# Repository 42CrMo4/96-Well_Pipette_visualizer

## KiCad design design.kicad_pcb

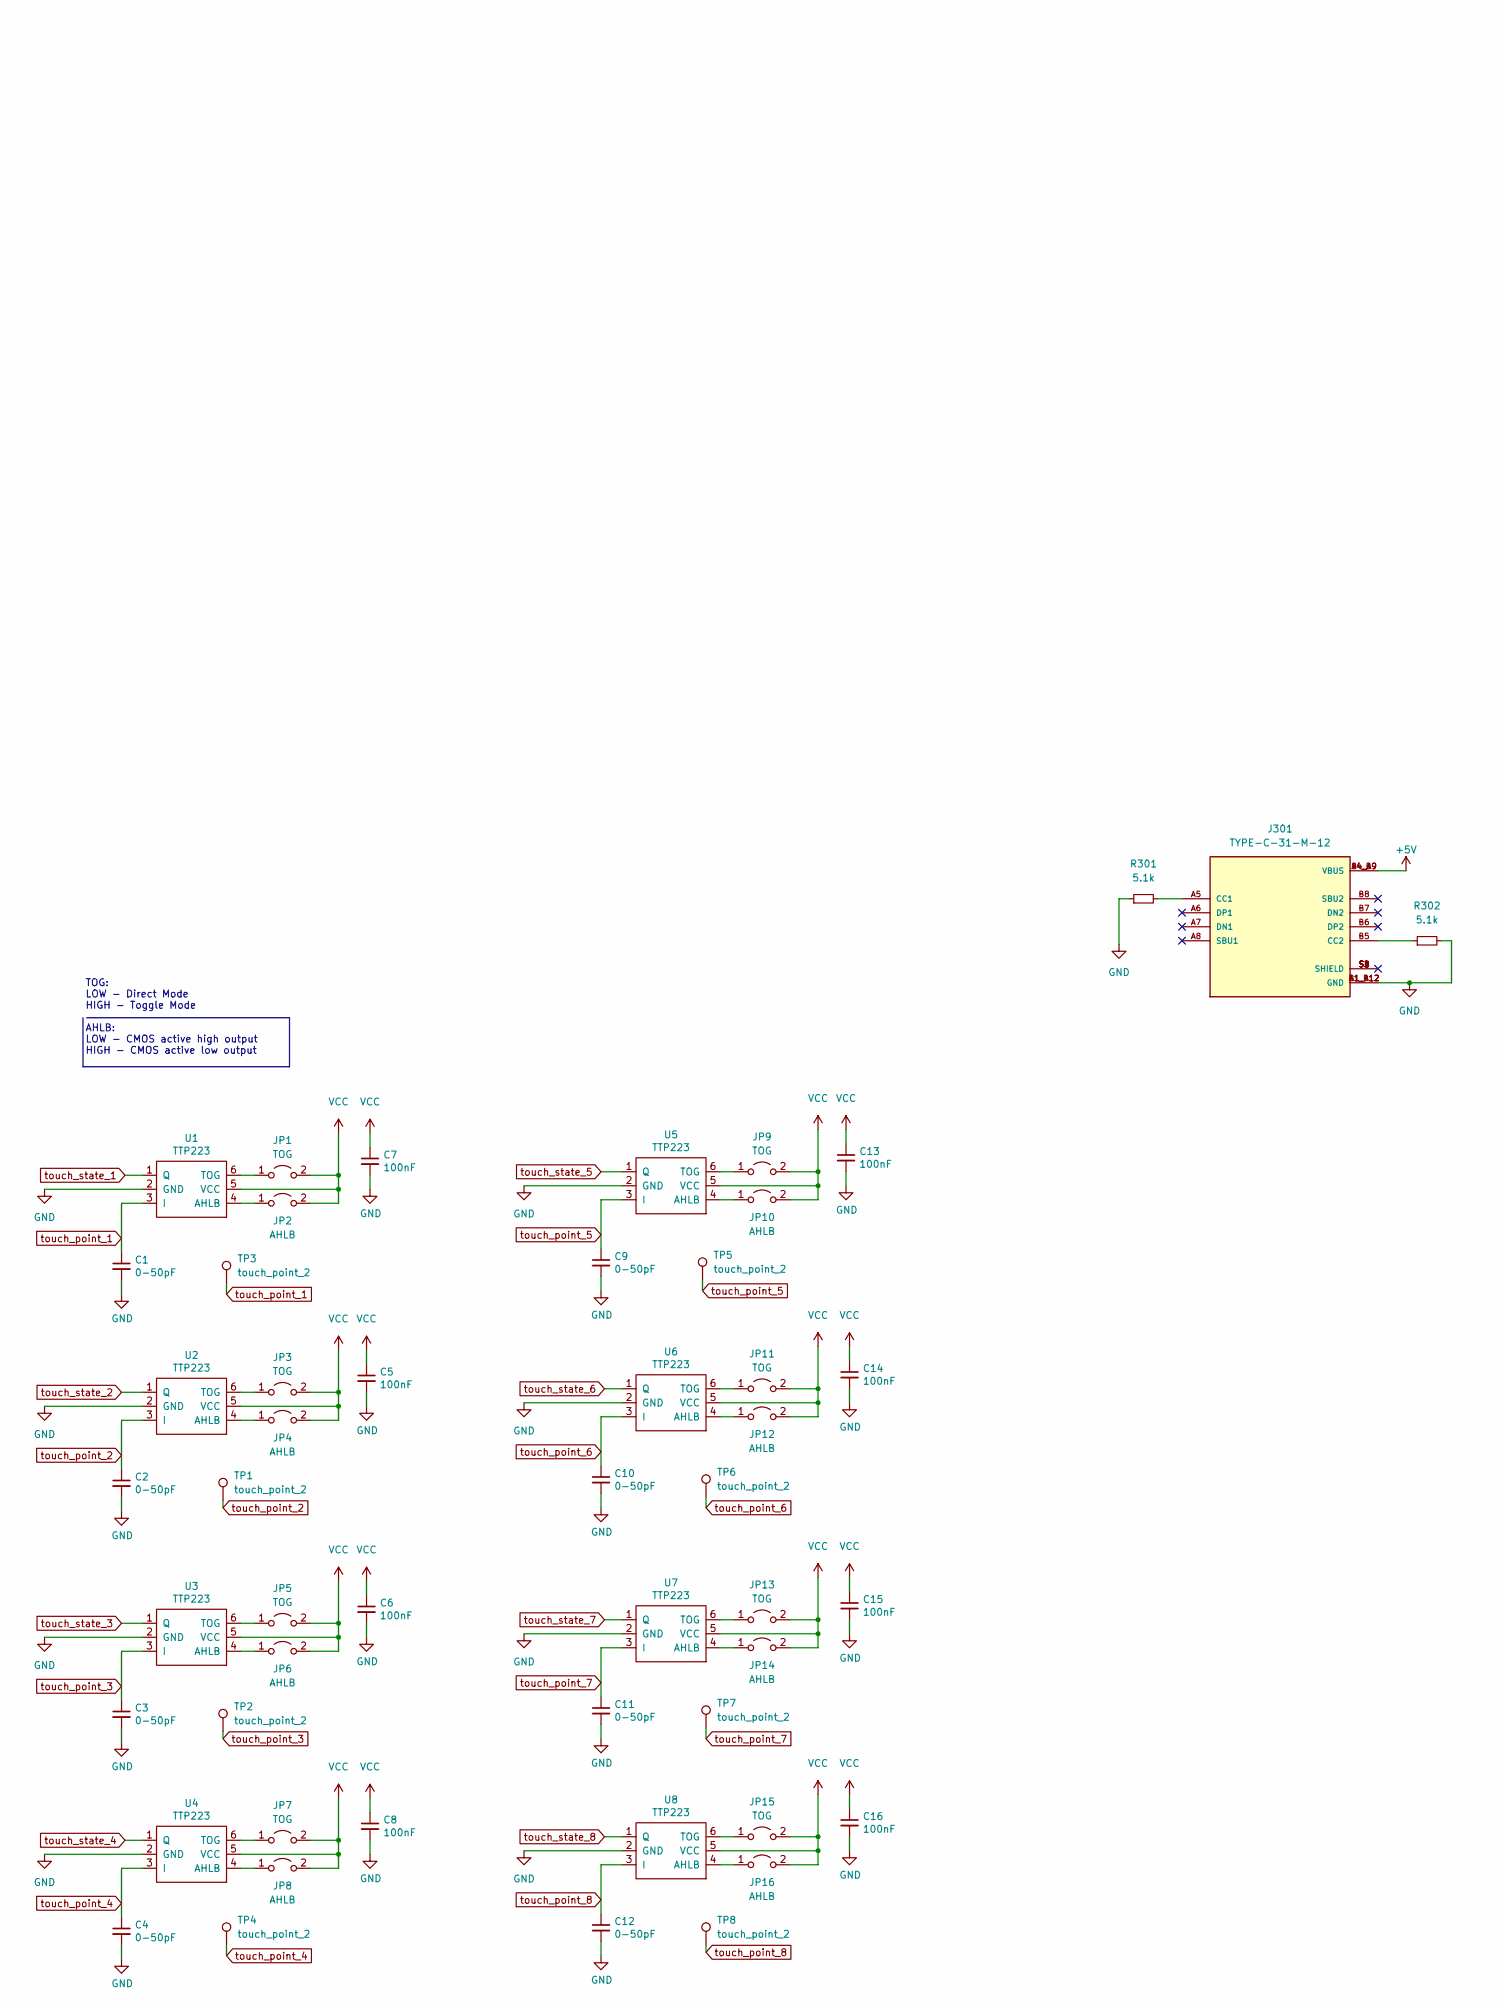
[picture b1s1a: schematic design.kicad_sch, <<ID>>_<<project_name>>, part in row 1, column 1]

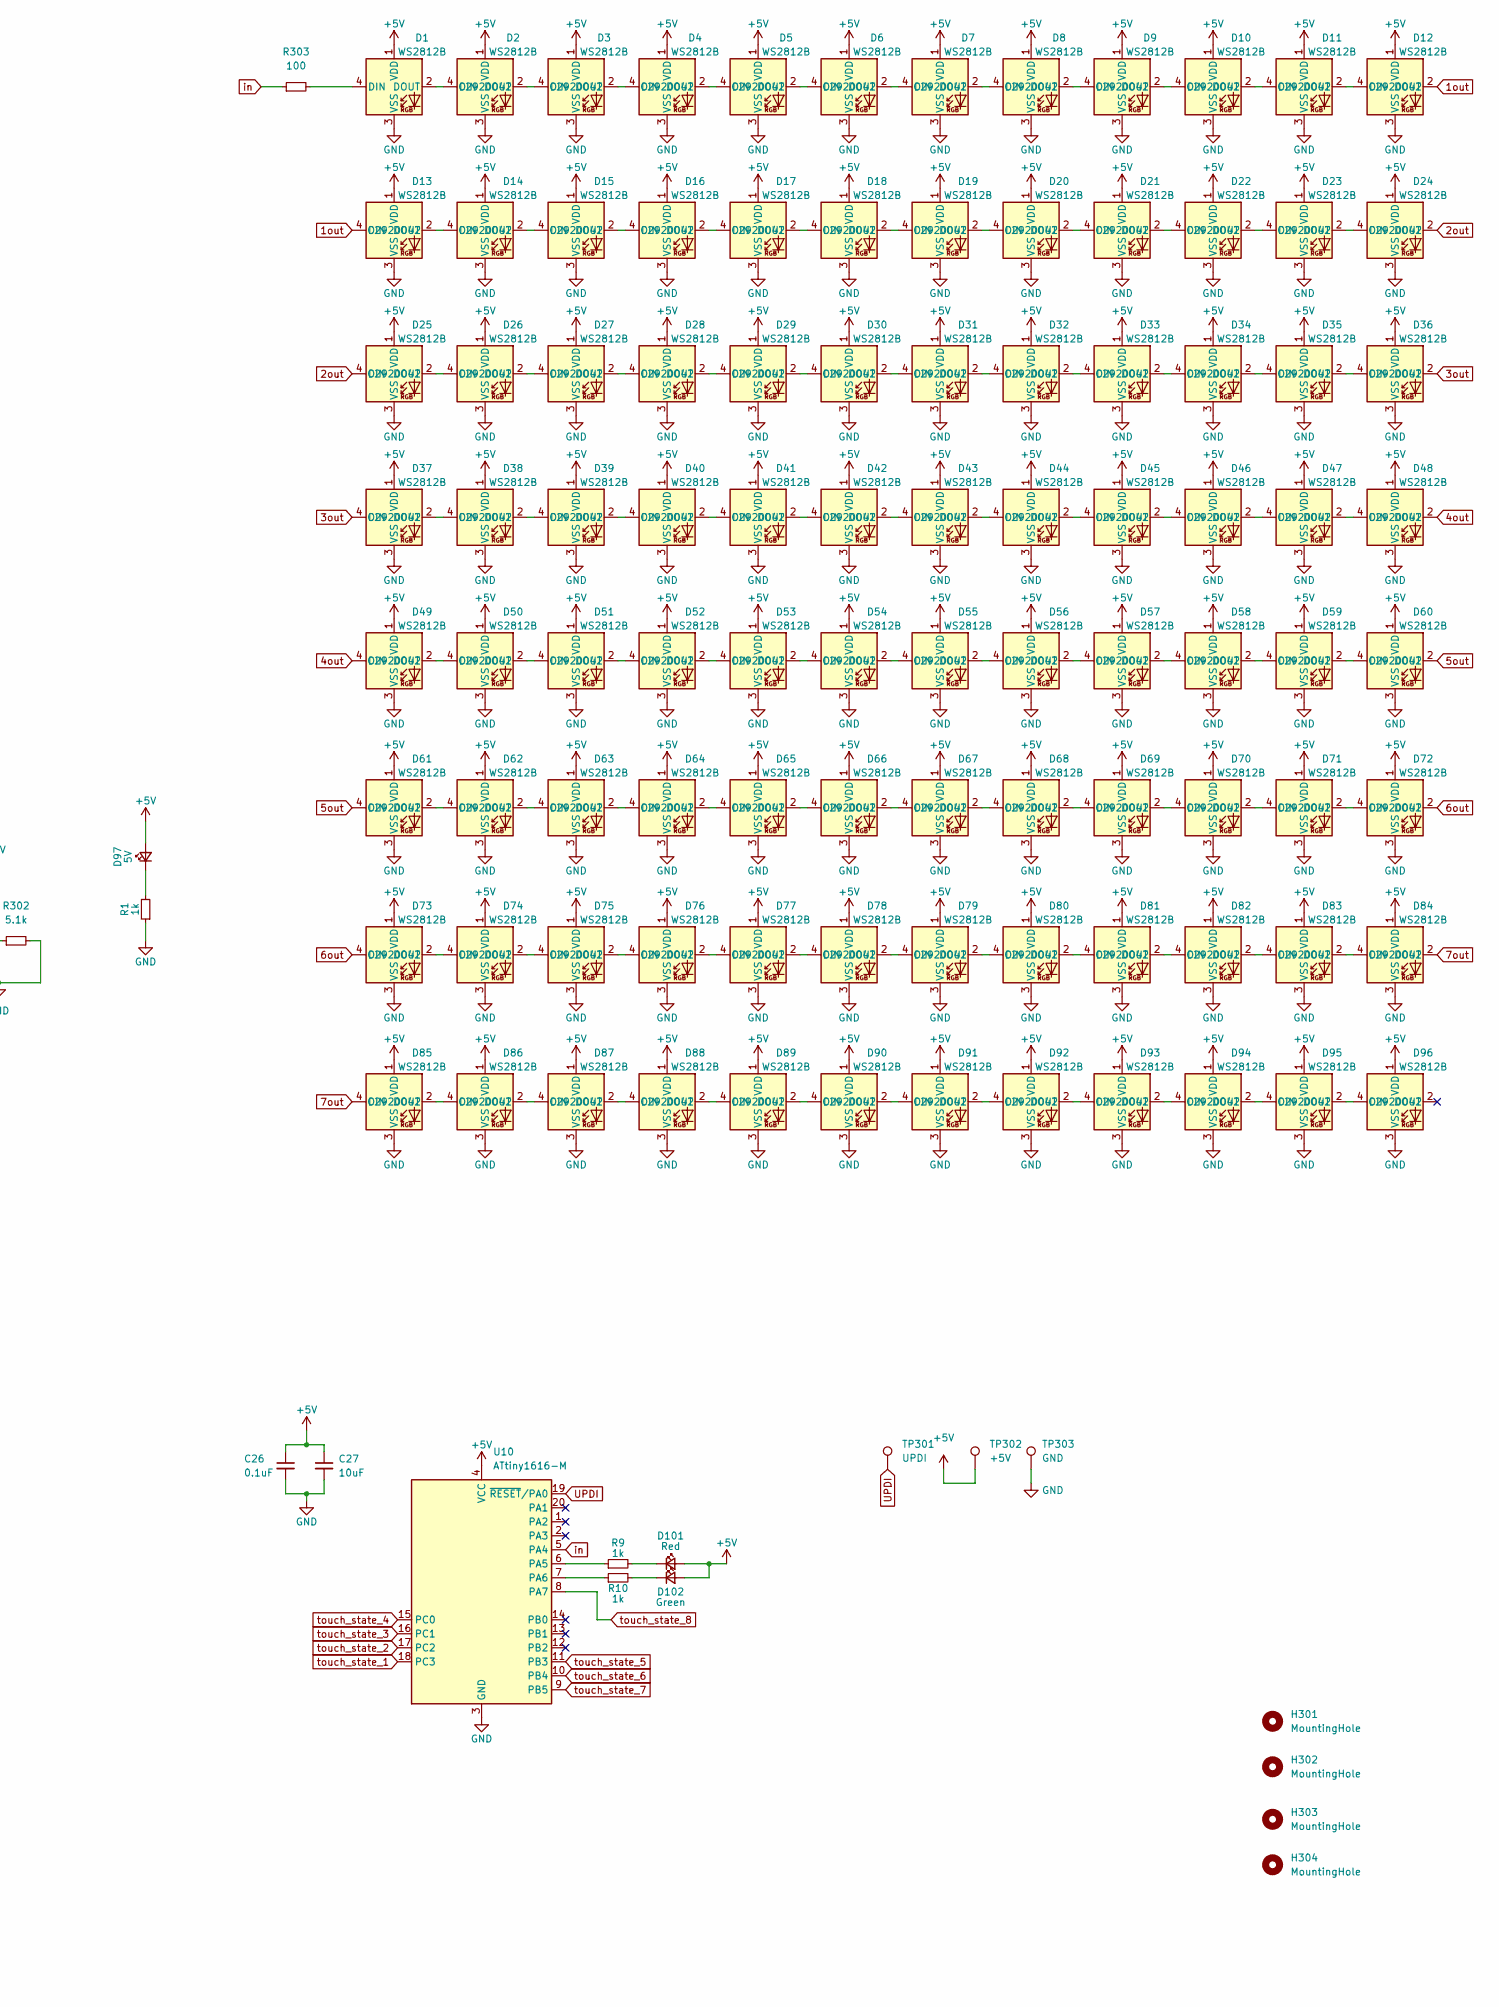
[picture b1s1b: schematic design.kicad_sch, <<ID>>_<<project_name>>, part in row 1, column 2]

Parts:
C1, C2, C3, C4, C9, C10, C11, C12: 0-50pF; C_0805_2012Metric
C5, C6, C7, C8, C13, C14, C15, C16: 100nF; C_0805_2012Metric
C26: 0.1uF; C_0805_2012Metric
C27: 10uF; C_0805_2012Metric
D1, D2, D3, D4, D5, D6, D7, D8, D9, D10, D11, D12, D13, D14, D15, D16, D17, D18, D19, D20, D21, D22, D23, D24, D25, D26, D27, D28, D29, D30, D31, D32, D33, D34, D35, D36, D37, D38, D39, D40, D41, D42, D43, D44, D45, D46, D47, D48, D49, D50, D51, D52, D53, D54, D55, D56, D57, D58, D59, D60, D61, D62, D63, D64, D65, D66, D67, D68, D69, D70, D71, D72, D73, D74, D75, D76, D77, D78, D79, D80, D81, D82, D83, D84, D85, D86, D87, D88, D89, D90, D91, D92, D93, D94, D95, D96: WS2812B; LED_WS2812B_PLCC4_5.0x5.0mm_P3.2mm; LCSC C2920042
D97: 5V; LED_0603_1608Metric
D101: Red; LED_0603_1608Metric
D102: Green; LED_0603_1608Metric
H301, H302, H303, H304: MountingHole; MountingHole_2.7mm_M2.5
J301: TYPE-C-31-M-12; TYPE-C-31-M-12_HRO_TYPE-C-31-M-12; PARTREV 2020.12.08
JP1, JP3, JP5, JP7, JP9, JP11, JP13, JP15: TOG; SolderJumper-2_P1.3mm_Open_RoundedPad1.0x1.5mm
JP2, JP4, JP6, JP8, JP10, JP12, JP14, JP16: AHLB; SolderJumper-2_P1.3mm_Open_RoundedPad1.0x1.5mm
R1, R9, R10: 1k; R_0805_2012Metric
R301, R302: 5.1k; R_0805_2012Metric
R303: 100; R_0805_2012Metric
TP1, TP2, TP3, TP4, TP5, TP6, TP7, TP8: touch_point_2
TP301: UPDI; TestPoint_Pad_3.0x3.0mm
TP302: +5V; TestPoint_Pad_3.0x3.0mm
TP303: GND; TestPoint_Pad_3.0x3.0mm
U1, U2, U3, U4, U5, U6, U7, U8: TTP223; SOT-23-6
U10: ATtiny1616-M; VQFN-20-1EP_3x3mm_P0.4mm_EP1.7x1.7mm

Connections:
1out: D12.2 (DOUT), D13.4 (DIN)
2out: D24.2 (DOUT), D25.4 (DIN)
3out: D36.2 (DOUT), D37.4 (DIN)
4out: D48.2 (DOUT), D49.4 (DIN)
5out: D60.2 (DOUT), D61.4 (DIN)
6out: D72.2 (DOUT), D73.4 (DIN)
7out: D84.2 (DOUT), D85.4 (DIN)
GND: C1.2, C2.2, C3.2, C4.2, C5.2, C6.2, C7.2, C8.2, C9.2, C10.2, C11.2, C12.2, C13.2, C14.2, C15.2, C16.2, C26.2, C27.2, D1.3 (VSS), D2.3 (VSS), D3.3 (VSS), D4.3 (VSS), D5.3 (VSS), D6.3 (VSS), D7.3 (VSS), D8.3 (VSS), D9.3 (VSS), D10.3 (VSS), D11.3 (VSS), D12.3 (VSS), D13.3 (VSS), D14.3 (VSS), D15.3 (VSS), D16.3 (VSS), D17.3 (VSS), D18.3 (VSS), D19.3 (VSS), D20.3 (VSS), D21.3 (VSS), D22.3 (VSS), D23.3 (VSS), D24.3 (VSS), D25.3 (VSS), D26.3 (VSS), D27.3 (VSS), D28.3 (VSS), D29.3 (VSS), D30.3 (VSS), D31.3 (VSS), D32.3 (VSS), D33.3 (VSS), D34.3 (VSS), D35.3 (VSS), D36.3 (VSS), D37.3 (VSS), D38.3 (VSS), D39.3 (VSS), D40.3 (VSS), D41.3 (VSS), D42.3 (VSS), D43.3 (VSS), D44.3 (VSS), D45.3 (VSS), D46.3 (VSS), D47.3 (VSS), D48.3 (VSS), D49.3 (VSS), D50.3 (VSS), D51.3 (VSS), D52.3 (VSS), D53.3 (VSS), D54.3 (VSS), D55.3 (VSS), D56.3 (VSS), D57.3 (VSS), D58.3 (VSS), D59.3 (VSS), D60.3 (VSS), D61.3 (VSS), D62.3 (VSS), D63.3 (VSS), D64.3 (VSS), D65.3 (VSS), D66.3 (VSS), D67.3 (VSS), D68.3 (VSS), D69.3 (VSS), D70.3 (VSS), D71.3 (VSS), D72.3 (VSS), D73.3 (VSS), D74.3 (VSS), D75.3 (VSS), D76.3 (VSS), D77.3 (VSS), D78.3 (VSS), D79.3 (VSS), D80.3 (VSS), D81.3 (VSS), D82.3 (VSS), D83.3 (VSS), D84.3 (VSS), D85.3 (VSS), D86.3 (VSS), D87.3 (VSS), D88.3 (VSS), D89.3 (VSS), D90.3 (VSS), D91.3 (VSS), D92.3 (VSS), D93.3 (VSS), D94.3 (VSS), D95.3 (VSS), D96.3 (VSS), J301.A1_B12 (GND), J301.B1_A12 (GND), R1.1, R301.1, R302.2, TP303.1, U1.2 (GND), U2.2 (GND), U3.2 (GND), U4.2 (GND), U5.2 (GND), U6.2 (GND), U7.2 (GND), U8.2 (GND), U10.3 (GND), U10.21 (GND)
unnamed: D1.2 (DOUT), D2.4 (DIN)
unnamed: D1.4 (DIN), R303.2
unnamed: D2.2 (DOUT), D3.4 (DIN)
unnamed: D3.2 (DOUT), D4.4 (DIN)
unnamed: D4.2 (DOUT), D5.4 (DIN)
unnamed: D5.2 (DOUT), D6.4 (DIN)
unnamed: D6.2 (DOUT), D7.4 (DIN)
unnamed: D7.2 (DOUT), D8.4 (DIN)
unnamed: D8.2 (DOUT), D9.4 (DIN)
unnamed: D10.2 (DOUT), D11.4 (DIN)
unnamed: D9.2 (DOUT), D10.4 (DIN)
unnamed: D11.2 (DOUT), D12.4 (DIN)
unnamed: D13.2 (DOUT), D14.4 (DIN)
unnamed: D14.2 (DOUT), D15.4 (DIN)
unnamed: D15.2 (DOUT), D16.4 (DIN)
unnamed: D16.2 (DOUT), D17.4 (DIN)
unnamed: D17.2 (DOUT), D18.4 (DIN)
unnamed: D18.2 (DOUT), D19.4 (DIN)
unnamed: D19.2 (DOUT), D20.4 (DIN)
unnamed: D20.2 (DOUT), D21.4 (DIN)
unnamed: D21.2 (DOUT), D22.4 (DIN)
unnamed: D22.2 (DOUT), D23.4 (DIN)
unnamed: D23.2 (DOUT), D24.4 (DIN)
unnamed: D25.2 (DOUT), D26.4 (DIN)
unnamed: D26.2 (DOUT), D27.4 (DIN)
unnamed: D27.2 (DOUT), D28.4 (DIN)
unnamed: D28.2 (DOUT), D29.4 (DIN)
unnamed: D29.2 (DOUT), D30.4 (DIN)
unnamed: D30.2 (DOUT), D31.4 (DIN)
unnamed: D31.2 (DOUT), D32.4 (DIN)
unnamed: D32.2 (DOUT), D33.4 (DIN)
unnamed: D33.2 (DOUT), D34.4 (DIN)
unnamed: D34.2 (DOUT), D35.4 (DIN)
unnamed: D35.2 (DOUT), D36.4 (DIN)
unnamed: D37.2 (DOUT), D38.4 (DIN)
unnamed: D38.2 (DOUT), D39.4 (DIN)
unnamed: D39.2 (DOUT), D40.4 (DIN)
unnamed: D40.2 (DOUT), D41.4 (DIN)
unnamed: D41.2 (DOUT), D42.4 (DIN)
unnamed: D42.2 (DOUT), D43.4 (DIN)
unnamed: D43.2 (DOUT), D44.4 (DIN)
unnamed: D44.2 (DOUT), D45.4 (DIN)
unnamed: D45.2 (DOUT), D46.4 (DIN)
unnamed: D46.2 (DOUT), D47.4 (DIN)
unnamed: D47.2 (DOUT), D48.4 (DIN)
unnamed: D49.2 (DOUT), D50.4 (DIN)
unnamed: D50.2 (DOUT), D51.4 (DIN)
unnamed: D51.2 (DOUT), D52.4 (DIN)
unnamed: D52.2 (DOUT), D53.4 (DIN)
unnamed: D53.2 (DOUT), D54.4 (DIN)
unnamed: D54.2 (DOUT), D55.4 (DIN)
unnamed: D55.2 (DOUT), D56.4 (DIN)
unnamed: D56.2 (DOUT), D57.4 (DIN)
unnamed: D57.2 (DOUT), D58.4 (DIN)
unnamed: D58.2 (DOUT), D59.4 (DIN)
unnamed: D59.2 (DOUT), D60.4 (DIN)
unnamed: D61.2 (DOUT), D62.4 (DIN)
unnamed: D62.2 (DOUT), D63.4 (DIN)
unnamed: D63.2 (DOUT), D64.4 (DIN)
unnamed: D64.2 (DOUT), D65.4 (DIN)
unnamed: D65.2 (DOUT), D66.4 (DIN)
unnamed: D66.2 (DOUT), D67.4 (DIN)
unnamed: D67.2 (DOUT), D68.4 (DIN)
unnamed: D68.2 (DOUT), D69.4 (DIN)
unnamed: D69.2 (DOUT), D70.4 (DIN)
unnamed: D70.2 (DOUT), D71.4 (DIN)
unnamed: D71.2 (DOUT), D72.4 (DIN)
unnamed: D73.2 (DOUT), D74.4 (DIN)
unnamed: D74.2 (DOUT), D75.4 (DIN)
unnamed: D75.2 (DOUT), D76.4 (DIN)
unnamed: D76.2 (DOUT), D77.4 (DIN)
unnamed: D77.2 (DOUT), D78.4 (DIN)
unnamed: D78.2 (DOUT), D79.4 (DIN)
unnamed: D79.2 (DOUT), D80.4 (DIN)
unnamed: D80.2 (DOUT), D81.4 (DIN)
unnamed: D81.2 (DOUT), D82.4 (DIN)
unnamed: D82.2 (DOUT), D83.4 (DIN)
unnamed: D83.2 (DOUT), D84.4 (DIN)
unnamed: D85.2 (DOUT), D86.4 (DIN)
unnamed: D86.2 (DOUT), D87.4 (DIN)
unnamed: D87.2 (DOUT), D88.4 (DIN)
unnamed: D88.2 (DOUT), D89.4 (DIN)
unnamed: D89.2 (DOUT), D90.4 (DIN)
unnamed: D90.2 (DOUT), D91.4 (DIN)
unnamed: D91.2 (DOUT), D92.4 (DIN)
unnamed: D92.2 (DOUT), D93.4 (DIN)
unnamed: D93.2 (DOUT), D94.4 (DIN)
unnamed: D94.2 (DOUT), D95.4 (DIN)
unnamed: D95.2 (DOUT), D96.4 (DIN)
unnamed: D97.1 (K), R1.2
unnamed: D101.1 (K), R9.2
unnamed: D102.1 (K), R10.2
unnamed: J301.A5 (CC1), R301.2
unnamed: J301.B5 (CC2), R302.1
unnamed: JP1.1 (A), U1.6 (TOG)
unnamed: JP2.1 (A), U1.4 (AHLB)
unnamed: JP3.1 (A), U2.6 (TOG)
unnamed: JP4.1 (A), U2.4 (AHLB)
unnamed: JP5.1 (A), U3.6 (TOG)
unnamed: JP6.1 (A), U3.4 (AHLB)
unnamed: JP7.1 (A), U4.6 (TOG)
unnamed: JP8.1 (A), U4.4 (AHLB)
unnamed: JP9.1 (A), U5.6 (TOG)
unnamed: JP10.1 (A), U5.4 (AHLB)
unnamed: JP11.1 (A), U6.6 (TOG)
unnamed: JP12.1 (A), U6.4 (AHLB)
unnamed: JP13.1 (A), U7.6 (TOG)
unnamed: JP14.1 (A), U7.4 (AHLB)
unnamed: JP15.1 (A), U8.6 (TOG)
unnamed: JP16.1 (A), U8.4 (AHLB)
unnamed: R9.1, U10.6 (PA5)
unnamed: R10.1, U10.7 (PA6)
UPDI: TP301.1, U10.19 (~RESET/PA0)
in: R303.1, U10.5 (PA4)
touch_point_1: C1.1, TP3.1, U1.3 (I)
touch_point_2: C2.1, TP1.1, U2.3 (I)
touch_point_3: C3.1, TP2.1, U3.3 (I)
touch_point_4: C4.1, TP4.1, U4.3 (I)
touch_point_5: C9.1, TP5.1, U5.3 (I)
touch_point_6: C10.1, TP6.1, U6.3 (I)
touch_point_7: C11.1, TP7.1, U7.3 (I)
touch_point_8: C12.1, TP8.1, U8.3 (I)
touch_state_1: U1.1 (Q), U10.18 (PC3)
touch_state_2: U2.1 (Q), U10.17 (PC2)
touch_state_3: U3.1 (Q), U10.16 (PC1)
touch_state_4: U4.1 (Q), U10.15 (PC0)
touch_state_5: U5.1 (Q), U10.11 (PB3)
touch_state_6: U6.1 (Q), U10.10 (PB4)
touch_state_7: U7.1 (Q), U10.9 (PB5)
touch_state_8: U8.1 (Q), U10.8 (PA7)

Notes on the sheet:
TOG: LOW - Direct Mode HIGH - Toggle Mode AHLB: LOW - CMOS active high output HIGH - CMOS active low output

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
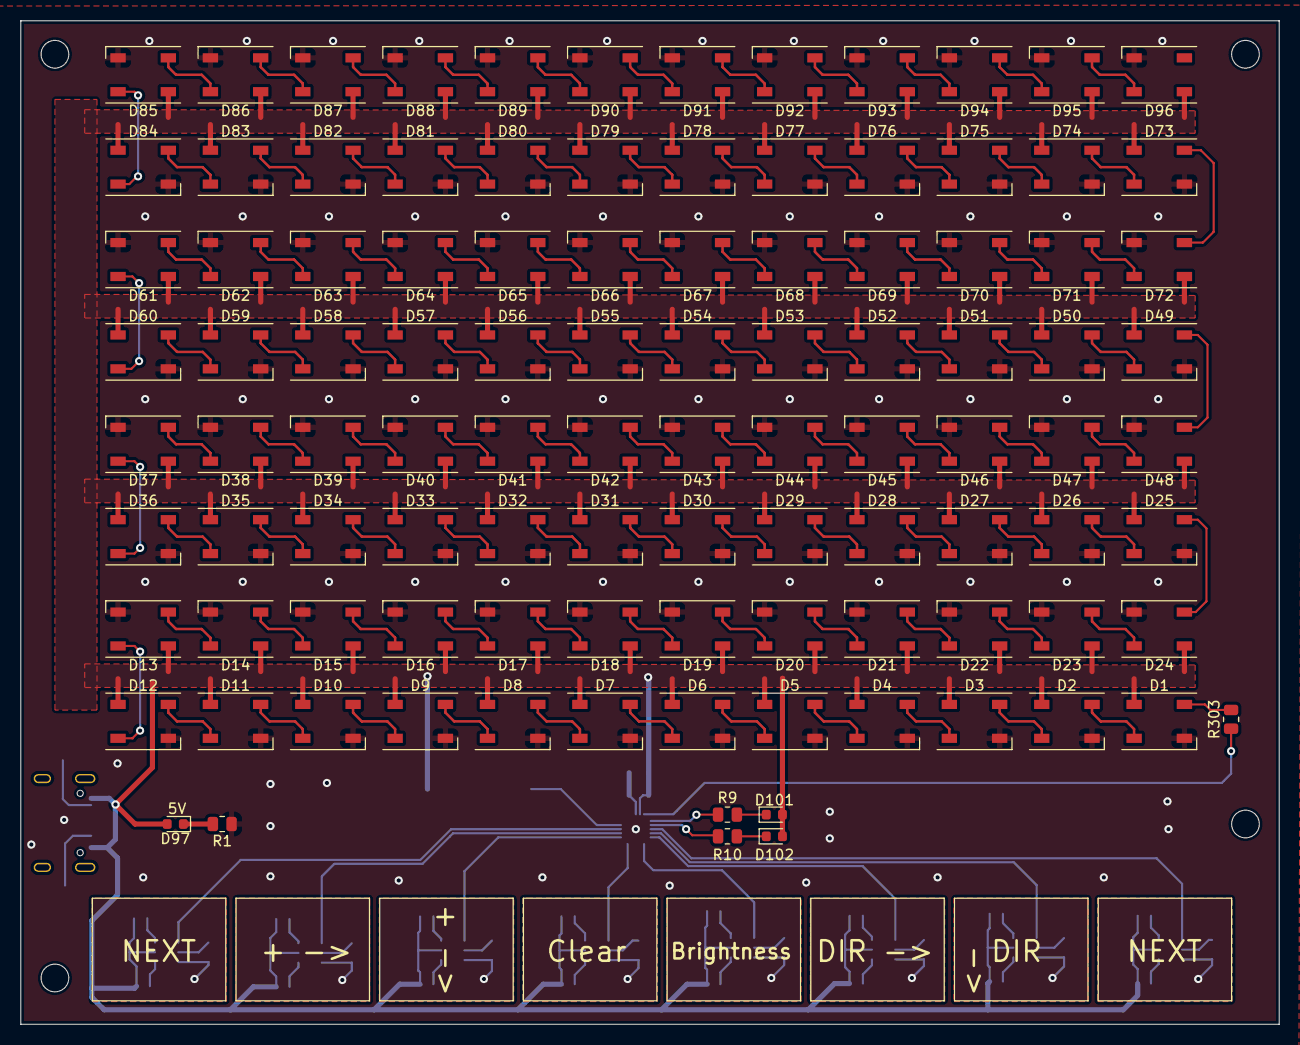
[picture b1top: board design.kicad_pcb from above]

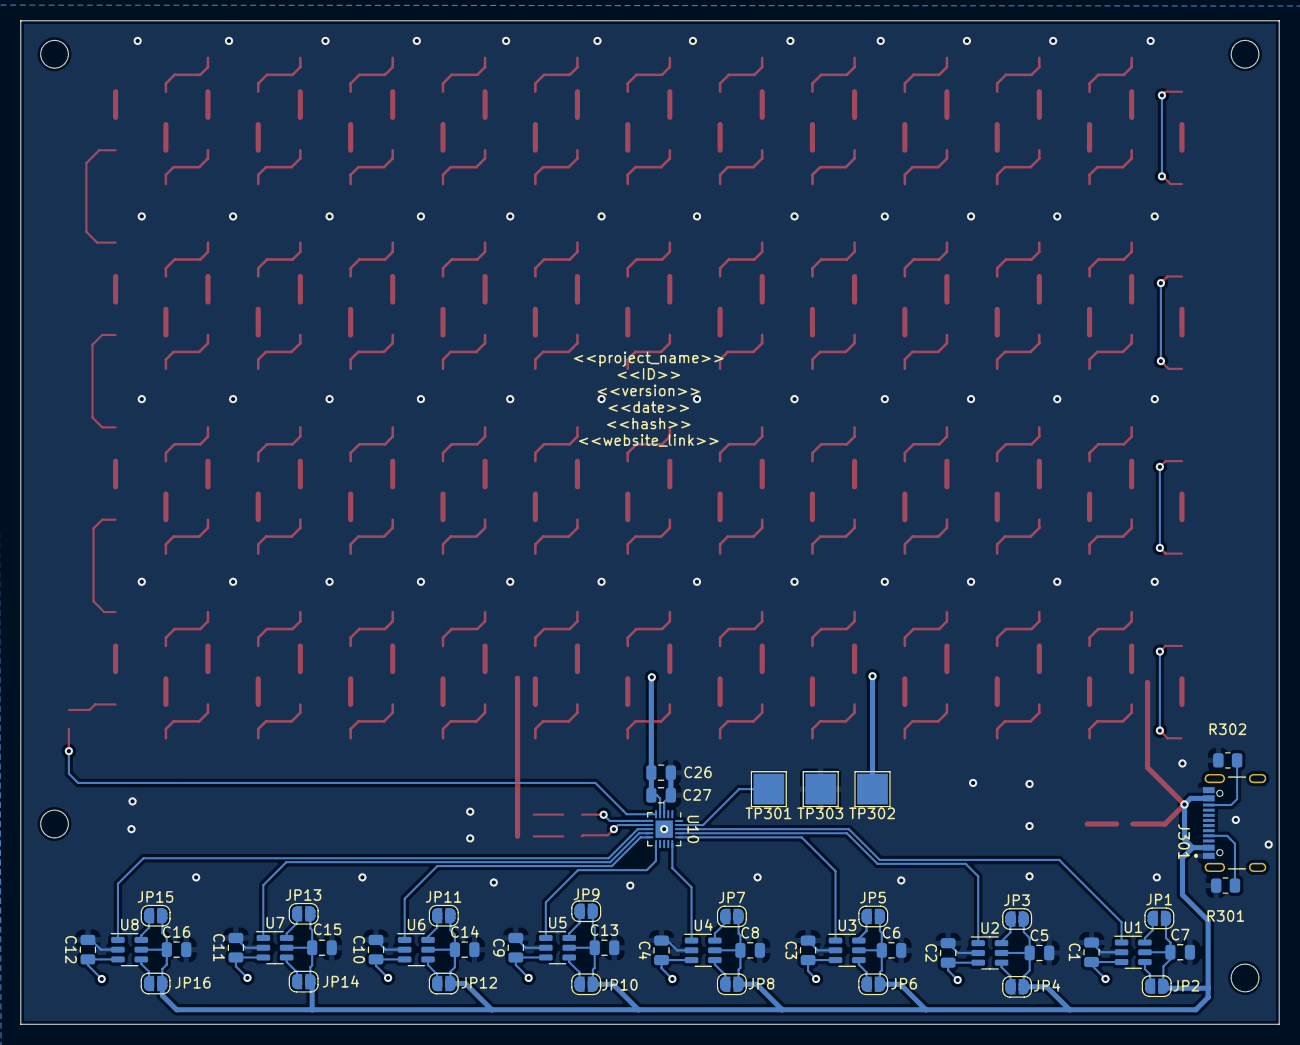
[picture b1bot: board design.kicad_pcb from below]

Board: 2 copper layers, 122.6 x 97.8 mm, 156 parts (49 on the bottom side), 139 nets.

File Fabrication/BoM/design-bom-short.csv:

Row,Description,Part,References,Value,Footprint,Quantity Per PCB,Status,Datasheet,LCSC,MF,MAXIMUM_PACKAGE_HEIGHT,Package,Price,Check_prices,STANDARD,PARTREV,SnapEDA_Link,MP,SNAPEDA_PN,Availability,MANUFACTURER
1,"Unpolarized capacitor, small symbol",C_Small,C5 C6 C7 C8 C13 C14 C15 C16 C26,100nF,C_0805_2012Metric,9, ,~,,,,,,,,,,,,,
2,"Unpolarized capacitor, small symbol",C_Small,C27,10uF,C_0805_2012Metric,1, ,~,,,,,,,,,,,,,
3,"Unpolarized capacitor, small symbol",C_Small,C1 C2 C3 C4 C9 C10 C11 C12,0-50pF,C_0805_2012Metric,8, ,~,,,,,,,,,,,,,
4,"Light emitting diode, small symbol",LED_Small,D97,5V,LED_0603_1608Metric,1, ,~,,,,,,,,,,,,,
5,"Light emitting diode, small symbol",LED_Small,D102,Green,LED_0603_1608Metric,1, ,~,,,,,,,,,,,,,
6,"Light emitting diode, small symbol",LED_Small,D101,Red,LED_0603_1608Metric,1, ,~,,,,,,,,,,,,,
7,RGB LED with integrated controller,WS2812B,D1 D2 D3 D4 D5 D6 D7 D8 D9 D10 D11 D12 D13 D14 D15 D16 D17 D18 D19 D20 D21 D22 D23 D24 D25 D26 D27 D28 D29 D30 D31 D32 D33 D34 D35 D36 D37 D38 D39 D40 D41 D42 D43 D44 D45 D46 D47 D48 D49 D50 D51 D52 D53 D54 D55 D56 D57 D58 D59 D60 D61 D62 D63 D64 D65 D66 D67 D68 D69 D70 D71 D72 D73 D74 D75 D76 D77 D78 D79 D80 D81 D82 D83 D84 D85 D86 D87 D88 D89 D90 D91 D92 D93 D94 D95 D96,WS2812B,LED_WS2812B_PLCC4_5.0x5.0mm_P3.2mm,96, ,https://cdn-shop.adafruit.com/datasheets/WS2812B.pdf,C2920042,,,,,,,,,,,,
8,USB Connectors 24 Receptacle 1 8.94*7.3mm RoHS,TYPE-C-31-M-12,J301,TYPE-C-31-M-12,TYPE-C-31-M-12_HRO_TYPE-C-31-M-12,1, ,,,"HRO Electronics Co., Ltd.",3.26 mm,Package,None,https://www.snapeda.com/parts/TYPE-C-31-M-12/HRO+Electronics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,Manufacturer Recommendations,2020.12.08,https://www.snapeda.com/parts/TYPE-C-31-M-12/HRO+Electronics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,TYPE-C-31-M-12,TYPE-C-31-M-12,Not in stock,"HRO Electronics Co., Ltd."
9,"Jumper, 2-pole, open",Jumper_2_Open,JP2 JP4 JP6 JP8 JP10 JP12 JP14 JP16,AHLB,SolderJumper-2_P1.3mm_Open_RoundedPad1.0x1.5mm,8, ,~,,,,,,,,,,,,,
10,"Jumper, 2-pole, open",Jumper_2_Open,JP1 JP3 JP5 JP7 JP9 JP11 JP13 JP15,TOG,SolderJumper-2_P1.3mm_Open_RoundedPad1.0x1.5mm,8, ,~,,,,,,,,,,,,,
11,"Resistor, small symbol",R_Small,R303,100,R_0805_2012Metric,1, ,~,,,,,,,,,,,,,
12,"Resistor, small symbol",R_Small,R1 R9 R10,1k,R_0805_2012Metric,3, ,~,,,,,,,,,,,,,
13,"Resistor, small symbol",R_Small,R301 R302,5.1k,R_0805_2012Metric,2, ,~,,,,,,,,,,,,,
14,"20MHz, 16kB Flash, 2kB SRAM, 256B EEPROM, VQFN-20",ATtiny1616-M,U10,ATtiny1616-M,VQFN-20-1EP_3x3mm_P0.4mm_EP1.7x1.7mm,1, ,http://ww1.microchip.com/downloads/en/DeviceDoc/ATtiny3216_A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,,,,,,,,,,,,,
15,,TTP223,U1 U2 U3 U4 U5 U6 U7 U8,TTP223,SOT-23-6,8, ,,,,,,,,,,,,,,

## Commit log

2024-04-14 remove diff
2024-04-14 use 8de6343 as workflow commit
2024-04-14 use tag v6.0 instead of commit
2024-05-04 lower clearance
2024-05-06 change to QFN 1616
2024-05-18 some confusing LED double footprints
2024-05-18 new layout
2024-05-18 add JLC output
2024-05-18 use v8 workflow?
2024-05-18 use kicad 8 branch of workflow
2024-05-18 upadte
2024-05-18 added lcsc number test
2024-05-18 update all LEDs with LCSC #
2024-05-19 mounting holes
2024-05-19 Test Ausrichtung
2024-05-19 mounting hole
2024-05-19 silkscreen correction
2024-05-19 Archive & Renew release docs
2024-06-06 added HW version Info
2024-06-06 Add Summary of code
2024-06-06 start to implement the button press feature
2024-06-06 Add simulated button press over UART
    Updated the code to include functionality for simulating a button press via UART. Now, besides physical button presses on pin 4, the program also responds to the character 'p' received over serial co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
2024-06-06 Factor out LED matrix definition to a separate file
    Created matrix.h to define the LED matrix separately from the main code. Updated the main code to reference the matrix from matrix.h, improving modularity and readability.
2024-06-06 Add brightness control via button and serial input
    Updated the code to include functionality for toggling between different brightness levels (10, 30, 50, 80, 100) using a second button and serial input. Added definitions for the brightness button an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
2024-06-06 Fix brightness control in lightUpMatrix function
    Updated the lightUpMatrix function to properly set brightness based on the currentBrightnessIndex. The brightness value is now correctly mapped and passed to the strip.setBrightness() call, ensuring 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
2024-06-06 Fix brightness setting and update immediately
    Modified the lightUpMatrix function to set the brightness after setting LED colors. Added a setBrightness function to update the brightness immediately when the brightness button is pressed, ensuring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
2024-06-06 Refactor brightness control and immediate brightness update
    Refactored the code to ensure the brightness is set immediately when toggled, rather than after the next button press. Improved function placement and clarity for setting the brightness and lighting 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
2024-06-06 Add button and serial option to toggle the number of LEDs lit
    Added a new button and serial option to toggle the "numLEDsLit" variable between the values 1, 2, 3, and 4. Updated the loop function to handle this new input and update the number of LEDs lit accord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
2024-06-06 Update numLEDsLit immediately when button is pressed
    Fixed the issue where the change in the number of LEDs lit was only visible after changing to the next set of LEDs. The update is now immediate upon button press or serial command.
2024-06-06 Add color change and clear matrix functionality
    Added functionality to change LED colors between red, green, and blue using a button or serial command. Also added a button and serial command to clear the matrix and start over.
2024-06-08 Refactor and enhance LED matrix control with button-only inputs
    - Removed all serial read functionality and handling to focus on button inputs for control.
2024-06-08 Fix color change behavior and update with button-only inputs
    - Enhanced color change functionality to not advance to the next LEDs, retaining the current LED position.
2024-06-08 Refactor to allow changing numLEDsLit at start
2024-06-08 color change fix
2024-06-08 light up first led(s) after clear
2024-06-08 add numLEDsLitOption with 6 LEDs
2024-06-08 add the other next button, update pins for pro mini
2024-06-17 changed VCC to +5V and connect them
2024-06-17 add series resistor
    closes #2
2024-06-17 cange usb-c footprints soldermask. add connections to shield.
2024-06-17 USB-C move shield to no NET
2024-06-17 Update Bom and PCB_top
2024-06-17 del unneeded
